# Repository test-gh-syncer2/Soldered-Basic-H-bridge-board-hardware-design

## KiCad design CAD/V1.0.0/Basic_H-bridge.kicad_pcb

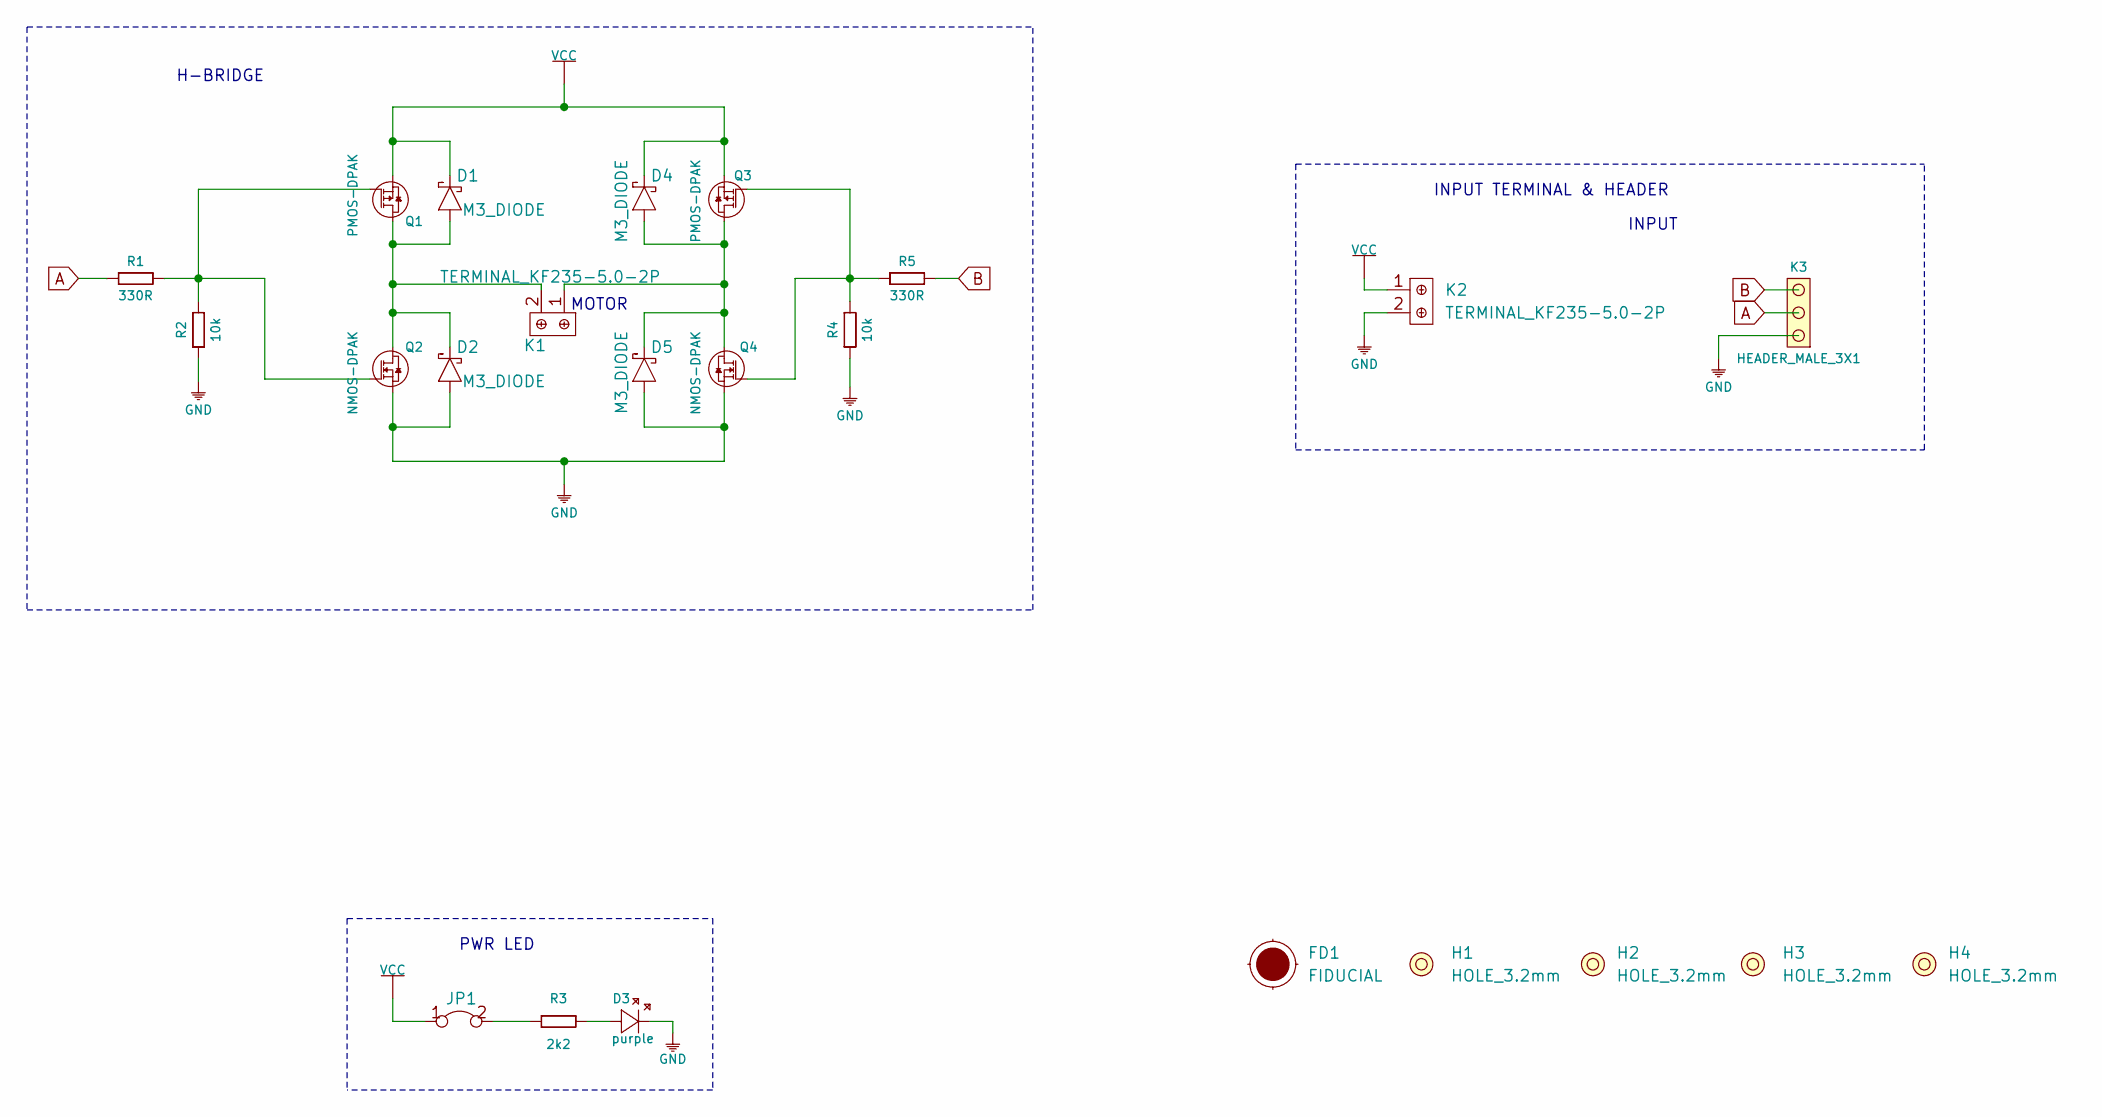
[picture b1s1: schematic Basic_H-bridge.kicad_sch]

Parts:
D1, D2, D4, D5: M3_DIODE; DO-214_DIODE
D3: purple; 0402LED
FD1: FIDUCIAL; FIDUCIAL_23
H1, H2, H3, H4: HOLE_3.2mm
JP1: SMD-JUMPER-CONNECTED_TRACE_SLODERMASK
K1, K2: TERMINAL_KF235-5.0-2P
K3: HEADER_MALE_3X1
Q1, Q3: PMOS-DPAK; DPAK
Q2, Q4: NMOS-DPAK; DPAK
R1, R5: 330R; 0603R
R2, R4: 10k; 0603R
R3: 2k2; 0402R

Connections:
A: K3.2, R1.1
B: K3.3, R5.2
GND: D2.1 (A), D3.2 (K), D5.1 (A), K2.2, K3.1, Q2.3 (S), Q4.3 (S), R2.1, R4.1
unnamed: D1.1 (A), D2.2 (K), K1.2, Q1.2 (D), Q2.2 (D)
unnamed: D3.1 (A), R3.2
unnamed: D4.1 (A), D5.2 (K), K1.1, Q3.2 (D), Q4.2 (D)
unnamed: JP1.2, R3.1
unnamed: Q1.1 (G), Q2.1 (G), R1.2, R2.2
unnamed: Q3.1 (G), Q4.1 (G), R4.2, R5.1
VCC: D1.2 (K), D4.2 (K), JP1.1, K2.1, Q1.3 (S), Q3.3 (S)

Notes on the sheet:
H-BRIDGE
PWR LED
MOTOR
INPUT TERMINAL & HEADER
INPUT

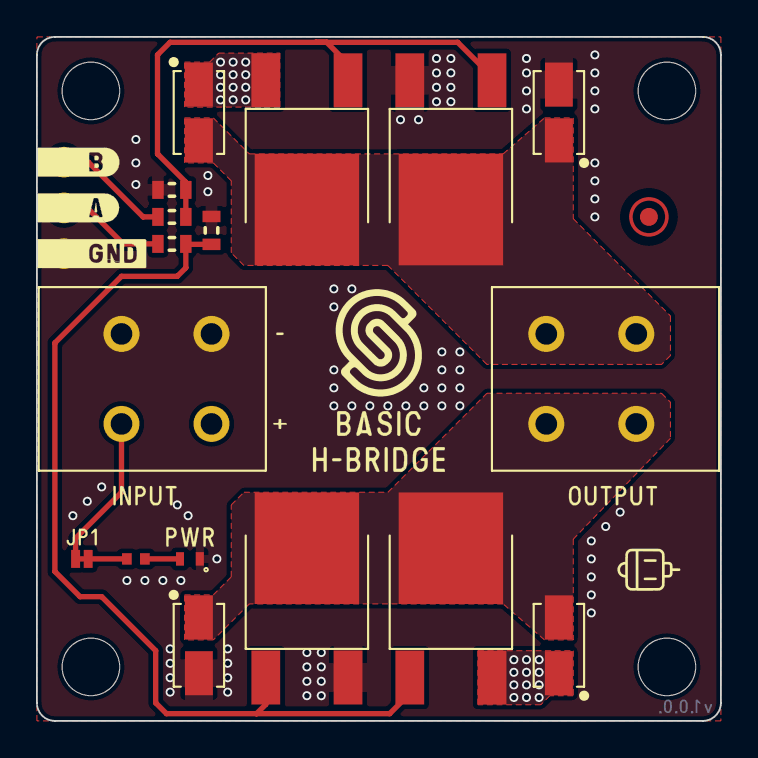
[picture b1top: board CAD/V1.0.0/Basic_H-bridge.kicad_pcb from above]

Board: 2 copper layers, 38.0 x 38.0 mm, 24 parts (1 on the bottom side), 10 nets.

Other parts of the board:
Ref**: Val**; Version1.0.0.

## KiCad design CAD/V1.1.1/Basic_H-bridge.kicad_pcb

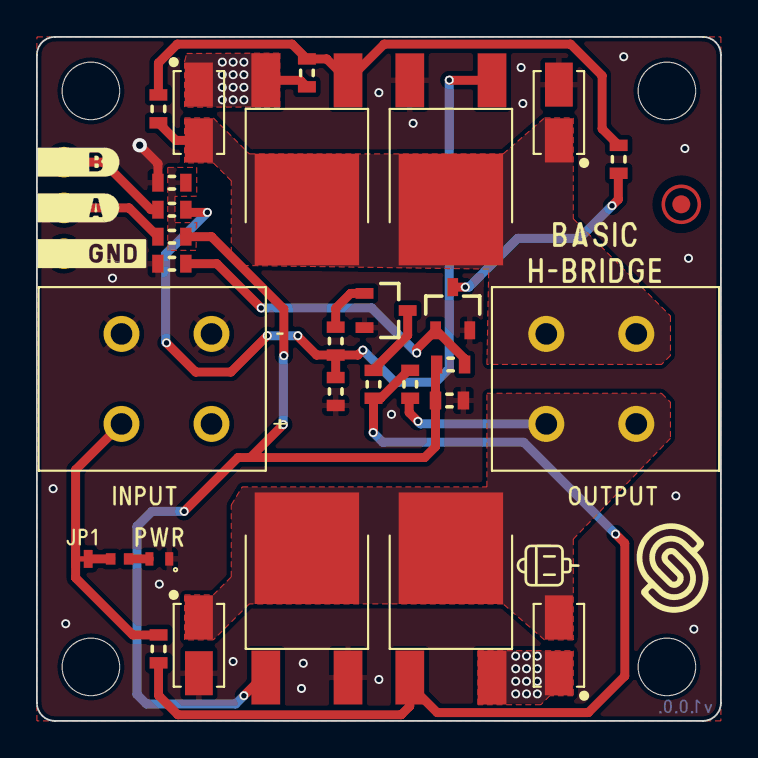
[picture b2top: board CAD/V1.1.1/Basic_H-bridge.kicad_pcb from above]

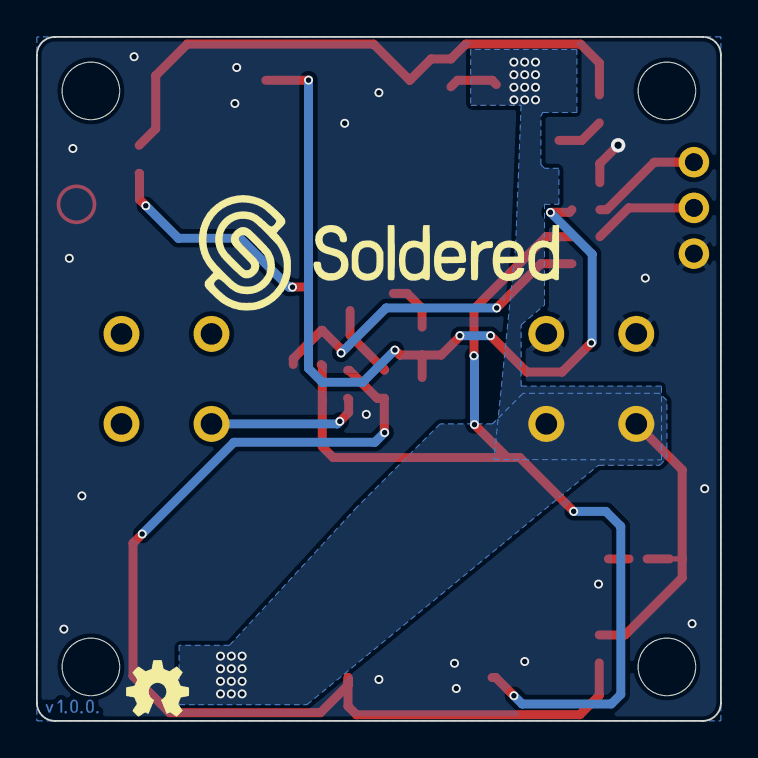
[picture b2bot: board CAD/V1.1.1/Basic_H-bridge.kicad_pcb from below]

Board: 2 copper layers, 38.0 x 38.0 mm, 36 parts (2 on the bottom side), 16 nets.

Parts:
D1, D2, D4, D5: M3_DIODE; DO-214_DIODE
D3: purple; 0402LED
FD1: FIDUCIAL; FIDUCIAL_23
H1, H2, H3, H4: HOLE_3.2mm
JP1: SMD-JUMPER-CONNECTED_TRACE_SLODERMASK
K1, K2: TERMINAL_KF235-5.0-2P
K3: HEADER_MALE_3X1
Q1, Q6: NPN-SOT-23-3; SOT-23-3
Q2, Q4: PMOS-DPAK; DPAK
Q3, Q5: NMOS-DPAK; DPAK
R1, R13: 330R; 0603R
R2, R2#2, R4, R4#2, R6, R8, R9, R12: 10k; 0603R
R3, R11: 1k; 0603R
R5: 1M; 0603R
R7: 2k2; 0402R
R10: 2M; 0603R
Ref**: Val**; Version1.0.0.

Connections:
A: K3.2, R1.1
B: K3.3, R13.2
GND: D2.1 (A), D3.2 (K), D5.1 (A), K2.2, K3.1, Q1.2 (E), Q3.3 (S), Q5.3 (S), Q6.2 (E), R2.1, R4#2.1, R6.1, R8.2
unnamed: D1.1 (A), D2.2 (K), K1.2, Q2.2 (D), Q3.2 (D), R5.1
unnamed: D3.1 (A), R7.2
unnamed: D4.1 (A), D5.2 (K), K1.1, Q4.2 (D), Q5.2 (D), R10.1
unnamed: JP1.2, R7.1
unnamed: Q1.1 (B), R2.2, R2#2.2
unnamed: Q1.3 (C), R11.2
unnamed: Q2.1 (G), R3.2, R4.1, R5.2
unnamed: Q3.1 (G), R1.2, R2#2.1, R4#2.2, R6.2
unnamed: Q4.1 (G), R9.2, R10.2, R11.1
unnamed: Q5.1 (G), R8.1, R12.2, R13.1
unnamed: Q6.1 (B), R12.1
unnamed: Q6.3 (C), R3.1
VCC: D1.2 (K), D4.2 (K), JP1.1, K2.1, Q2.3 (S), Q4.3 (S), R4.2, R9.1

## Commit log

2021-09-23 Syncing to git
2021-09-23 Updating open source files.
